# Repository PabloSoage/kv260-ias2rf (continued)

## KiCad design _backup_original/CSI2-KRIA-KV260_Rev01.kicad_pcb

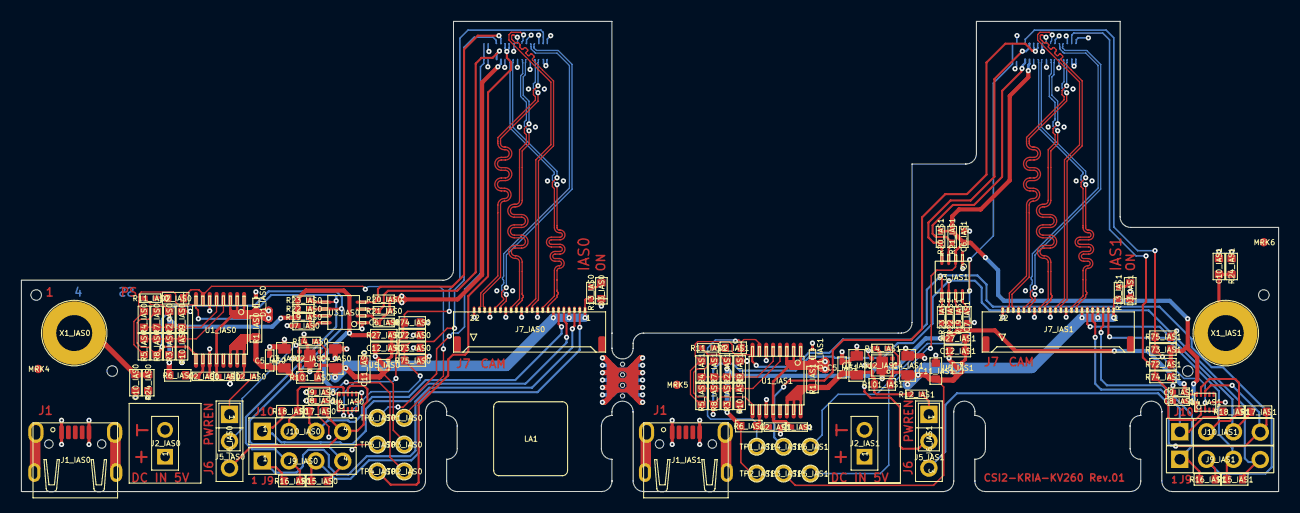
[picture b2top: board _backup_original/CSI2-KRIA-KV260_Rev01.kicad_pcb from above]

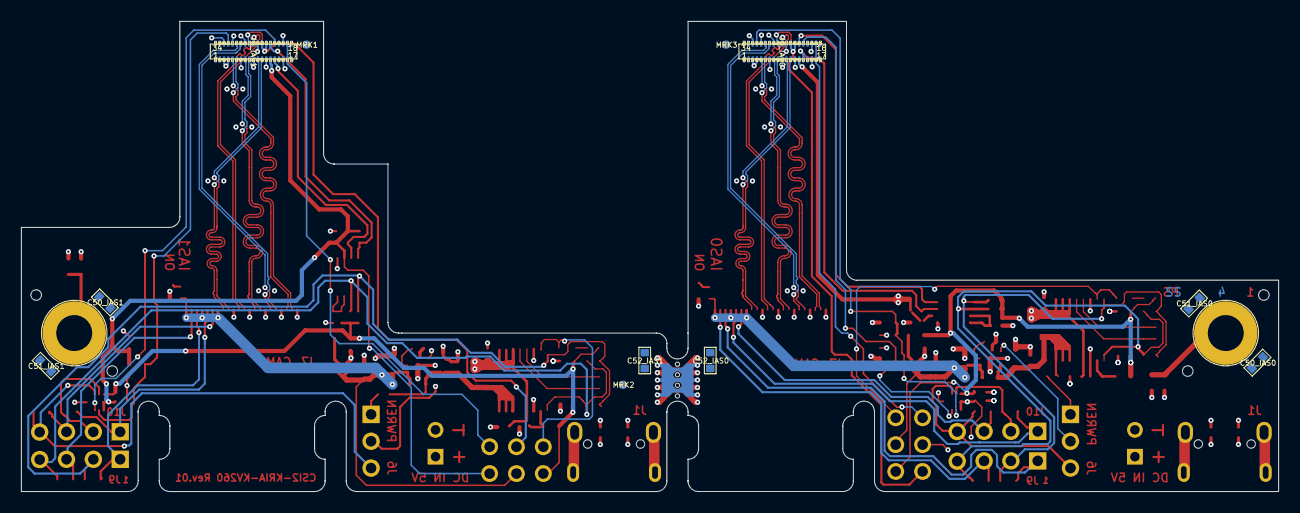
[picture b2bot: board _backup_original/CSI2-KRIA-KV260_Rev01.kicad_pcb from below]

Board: 4 copper layers, 119.0 x 44.5 mm, 145 parts (12 on the bottom side), 82 nets.

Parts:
C1_IAS0, C1_IAS1, C2_IAS0, C2_IAS1: NL; C-0402_0.55
C3_IAS0, C3_IAS1, C4_IAS0, C4_IAS1: 10u; C-0805_1.4
C5_IAS0, C5_IAS1, C6_IAS0, C6_IAS1, C8_IAS0, C8_IAS1, C9_IAS0, C9_IAS1: 100n; C-0402_0.55
C7_IAS0, C7_IAS1: 100p; C-0402_0.55
C10_IAS0, C10_IAS1: NL; C-0603_1.0
C11_IAS0, C11_IAS1, C12_IAS0, C12_IAS1, C50_IAS0, C50_IAS1, C51_IAS0, C51_IAS1, C52_IAS0, C52_IAS1: 4u7; C-0603_1.0
D1_IAS0, D1_IAS1: ESD9B5.0ST5G; D-SOD923
D2_IAS0, D2_IAS1: RED; D-0603-LED
D3_IAS0, D3_IAS1: GREEN; D-0603-LED
J1_IAS0, J1_IAS1: USB 2.0 Typ B 90°; J-629105150521
J2_IAS0, J2_IAS1: CON1x2; CON 1x2 RM2.54
J5_IAS0, J5_IAS1: Jumper; J-JUMPER-2.54
J6_IAS0, J6_IAS1: CON1x3; CON 1x3 RM2.54
J7_IAS0, J7_IAS1: CON FFC22_Inverted; J-FH55-22S-0.5SH - Inverted Pins
J8_IAS0, J8_IAS1: BM20B(0.8)-34DP-0.4V(51); J-BM20B(0.8)-34DP
J9_IAS0, J9_IAS1, J10_IAS0, J10_IAS1: CON1x4; CON 1x4 RM2.54
LA1: LABEL 7x7mm; PCB LABEL 7x7
MRK1, MRK2, MRK3: Marker Single Layer; PCB_Marker_Pad_top
MRK4, MRK5, MRK6: Marker Single Layer; PCB_MARKER_PAD_TOP
R1_IAS0, R1_IAS1, R3_IAS0, R3_IAS1, R9_IAS0, R9_IAS1, R15_IAS0, R15_IAS1, R16_IAS0, R16_IAS1, R24_IAS0, R24_IAS1, R27_IAS0, R27_IAS1: 0R0; R-0603_0.6
R2_IAS0, R2_IAS1, R4_IAS0, R4_IAS1, R5_IAS0, R5_IAS1, R6_IAS0, R6_IAS1, R7_IAS0, R7_IAS1, R8_IAS0, R8_IAS1, R10_IAS0, R10_IAS1, R17_IAS0, R17_IAS1, R18_IAS0, R18_IAS1, R72_IAS0, R72_IAS1, R73_IAS0, R73_IAS1, R74_IAS0, R74_IAS1, R75_IAS0, R75_IAS1, R101_IAS0, R101_IAS1: NL; R-0603_0.6
R11_IAS0, R11_IAS1: NL; R-0402_0.4
R12_IAS0: 270k; R-0402_0.4
R12_IAS1: 270K; R-0402_0.4
R13_IAS0, R13_IAS1: 3k3; R-0402_0.4
R14_IAS0, R14_IAS1: 51k; R-0402_0.4
R19_IAS0, R19_IAS1: 200k; R-0402_0.4
R20_IAS0, R20_IAS1, R21_IAS0, R21_IAS1, R22_IAS0, R22_IAS1, R23_IAS0, R23_IAS1: 2k0; R-0402_0.4
T1: PCB Text TOP; PCB TEXTFIELD TOP 2
T2: PCB Text BOT; PCB TEXTFIELD BOT 2
TP1_IAS0, TP1_IAS1, TP2_IAS0, TP2_IAS1, TP3_IAS0, TP3_IAS1, TP4_IAS0, TP4_IAS1, TP5_IAS0, TP5_IAS1, TP6_IAS0, TP6_IAS1: TP; TP_16_10
U1_IAS0, U1_IAS1: INA260AIPWR; IC-TSSOP16 6.4x5.1x1.2
U2_IAS0, U2_IAS1: TPS25200DRVT; IC-DFN06_2.0x2.0x0.8
U3_IAS0, U3_IAS1: PCA9306DCTR; IC-TSSOP8_3.15x4.25x1.3
U4_IAS0, U4_IAS1: NTB0104GU12,115; IC-XQFN12_1.7x2x0.5
U5_IAS0, U5_IAS1: NCP114AMX330TCG; IC-XDFN4_1.0x1.0x0.6
X1_IAS0, X1_IAS1: Hole; HOLE-3.4-6.0-DK

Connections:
B7-CSI2-TXC_IAS0_N: J7_IAS0.14, J8_IAS0.8
B7-CSI2-TXC_IAS0_P: J7_IAS0.15, J8_IAS0.7
B7-CSI2-TXC_IAS1_N: J7_IAS1.14, J8_IAS1.8
B7-CSI2-TXC_IAS1_P: J7_IAS1.15, J8_IAS1.7
B7-CSI2-TXD0_IAS0_N: J7_IAS0.20, J8_IAS0.5
B7-CSI2-TXD0_IAS0_P: J7_IAS0.21, J8_IAS0.4
B7-CSI2-TXD0_IAS1_N: J7_IAS1.20, J8_IAS1.5
B7-CSI2-TXD0_IAS1_P: J7_IAS1.21, J8_IAS1.4
B7-CSI2-TXD1_IAS0_N: J7_IAS0.17, J8_IAS0.29
B7-CSI2-TXD1_IAS0_P: J7_IAS0.18, J8_IAS0.30
B7-CSI2-TXD1_IAS1_N: J7_IAS1.17, J8_IAS1.29
B7-CSI2-TXD1_IAS1_P: J7_IAS1.18, J8_IAS1.30
B7-CSI2-TXD2_IAS0_N: J7_IAS0.11, J8_IAS0.26
B7-CSI2-TXD2_IAS0_P: J7_IAS0.12, J8_IAS0.27
B7-CSI2-TXD2_IAS1_N: J7_IAS1.11, J8_IAS1.26
B7-CSI2-TXD2_IAS1_P: J7_IAS1.12, J8_IAS1.27
B7-CSI2-TXD3_IAS0_N: J7_IAS0.8, J8_IAS0.11
B7-CSI2-TXD3_IAS0_P: J7_IAS0.9, J8_IAS0.10
B7-CSI2-TXD3_IAS1_N: J7_IAS1.8, J8_IAS1.11
B7-CSI2-TXD3_IAS1_P: J7_IAS1.9, J8_IAS1.10
C-GND_IAS0: C10_IAS0.2, J1_IAS0.6, J1_IAS0.7, J1_IAS0.8, J1_IAS0.9, R24_IAS0.1, X1_IAS0.1
C-GND_IAS1: C10_IAS1.2, J1_IAS1.6, J1_IAS1.7, J1_IAS1.8, J1_IAS1.9, R24_IAS1.1, X1_IAS1.1
EXT-GPIO0-I2C-SCL_IAS0: J7_IAS0.2, J9_IAS0.3, R15_IAS0.1
EXT-GPIO0-I2C-SCL_IAS1: J7_IAS1.2, J9_IAS1.3, R15_IAS1.1
EXT-GPIO1-I2C-SDA_IAS0: J7_IAS0.3, J9_IAS0.1, R16_IAS0.1
EXT-GPIO1-I2C-SDA_IAS1: J7_IAS1.3, J9_IAS1.1, R16_IAS1.1
EXT-GPIO2_IAS0: J7_IAS0.5, J10_IAS0.1, R18_IAS0.1
EXT-GPIO2_IAS1: J7_IAS1.5, J10_IAS1.1, R18_IAS1.1
EXT-GPIO3_IAS0: J7_IAS0.6, J10_IAS0.3, R17_IAS0.1
EXT-GPIO3_IAS1: J7_IAS1.6, J10_IAS1.3, R17_IAS1.1
GND: C1_IAS0.2, C1_IAS1.2, C2_IAS0.2, C2_IAS1.2, C3_IAS0.2, C3_IAS1.2, C4_IAS0.2, C4_IAS1.2, C5_IAS0.2, C5_IAS1.2, C6_IAS0.2, C6_IAS1.2, C7_IAS0.2, C7_IAS1.2, C8_IAS0.2, C8_IAS1.2, C9_IAS0.2, C9_IAS1.2, C10_IAS0.1, C10_IAS1.1, C11_IAS0.2, C11_IAS1.2, C12_IAS0.2, C12_IAS1.2, D1_IAS0.A, D1_IAS1.A, D3_IAS0.K, D3_IAS1.K, J1_IAS0.5, J1_IAS1.5, J2_IAS0.2, J2_IAS1.2, J7_IAS0.10, J7_IAS0.13, J7_IAS0.16, J7_IAS0.19, J7_IAS0.22, J7_IAS1.10, J7_IAS1.13, J7_IAS1.16, J7_IAS1.19, J7_IAS1.22, J8_IAS0.2, J8_IAS0.3, J8_IAS0.6, J8_IAS0.9, J8_IAS0.12, J8_IAS0.16, J8_IAS0.19, J8_IAS0.25, J8_IAS0.28, J8_IAS0.31, J8_IAS0.33, J8_IAS1.2, J8_IAS1.3, J8_IAS1.6, J8_IAS1.9, J8_IAS1.12, J8_IAS1.16, J8_IAS1.19, J8_IAS1.25, J8_IAS1.28, J8_IAS1.31, J8_IAS1.33, R9_IAS0.1, R9_IAS1.1, R10_IAS0.1, R10_IAS1.1, R14_IAS0.1, R14_IAS1.1, R24_IAS0.2, R24_IAS1.2, R74_IAS0.1, R74_IAS1.1, R75_IAS0.1, R75_IAS1.1, U1_IAS0.6, U1_IAS0.11, U1_IAS1.6, U1_IAS1.11, U2_IAS0.5, U2_IAS0.7, U2_IAS1.5, U2_IAS1.7, U3_IAS0.1, U3_IAS1.1, U4_IAS0.6, U4_IAS1.6, U5_IAS0.2, U5_IAS0.5, U5_IAS1.2, U5_IAS1.5
GPIO2_3V3_IAS0: J10_IAS0.2, R18_IAS0.2, U4_IAS0.10
GPIO2_3V3_IAS1: J10_IAS1.2, R18_IAS1.2, U4_IAS1.10
GPIO2_IAS0: J8_IAS0.32, R72_IAS0.1, R74_IAS0.2, U4_IAS0.2
GPIO2_IAS1: J8_IAS1.32, R72_IAS1.1, R74_IAS1.2, U4_IAS1.2
GPIO3_3V3_IAS0: J6_IAS0.3, J10_IAS0.4, R17_IAS0.2, U4_IAS0.9
GPIO3_3V3_IAS1: J6_IAS1.3, J10_IAS1.4, R17_IAS1.2, U4_IAS1.9
I2C_SCL_3V3_IAS0: J9_IAS0.4, R7_IAS0.1, R8_IAS0.1, R15_IAS0.2, R22_IAS0.1, U1_IAS0.9, U3_IAS0.6
I2C_SCL_3V3_IAS1: J9_IAS1.4, R7_IAS1.1, R8_IAS1.1, R15_IAS1.2, R22_IAS1.1, U1_IAS1.9, U3_IAS1.6
I2C_SCL_IAS0: J8_IAS0.14, R21_IAS0.2, U3_IAS0.3
I2C_SCL_IAS1: J8_IAS1.14, R21_IAS1.2, U3_IAS1.3
I2C_SDA_3V3_IAS0: J9_IAS0.2, R4_IAS0.1, R5_IAS0.1, R16_IAS0.2, R23_IAS0.1, U1_IAS0.8, U3_IAS0.5
I2C_SDA_3V3_IAS1: J9_IAS1.2, R4_IAS1.1, R5_IAS1.1, R16_IAS1.2, R23_IAS1.1, U1_IAS1.8, U3_IAS1.5
I2C_SDA_IAS0: J8_IAS0.22, R20_IAS0.2, U3_IAS0.4
I2C_SDA_IAS1: J8_IAS1.22, R20_IAS1.2, U3_IAS1.4
INA260-A0_IAS0: R2_IAS0.2, R4_IAS0.2, R7_IAS0.2, R9_IAS0.2, U1_IAS0.5
INA260-A0_IAS1: R2_IAS1.2, R4_IAS1.2, R7_IAS1.2, R9_IAS1.2, U1_IAS1.5
INA260-A1_IAS0: R3_IAS0.2, R5_IAS0.2, R8_IAS0.2, R10_IAS0.2, U1_IAS0.4
INA260-A1_IAS1: R3_IAS1.2, R5_IAS1.2, R8_IAS1.2, R10_IAS1.2, U1_IAS1.4
NetC2_IAS0_1: C2_IAS0.1, R6_IAS0.2, U1_IAS0.10
NetC2_IAS1_1: C2_IAS1.1, R6_IAS1.2, U1_IAS1.10
NetC7_IAS0_1: C7_IAS0.1, R19_IAS0.1, U3_IAS0.7, U3_IAS0.8
NetC7_IAS1_1: C7_IAS1.1, R19_IAS1.1, U3_IAS1.7, U3_IAS1.8
NetC12_IAS0_1: C12_IAS0.1, R27_IAS0.1, U5_IAS0.1
NetC12_IAS1_1: C12_IAS1.1, R27_IAS1.1, U5_IAS1.1
NetD2_IAS0_A: D2_IAS0.A, R11_IAS0.2
NetD2_IAS0_K: D2_IAS0.K, TP1_IAS0.1, U1_IAS0.7
NetD2_IAS1_A: D2_IAS1.A, R11_IAS1.2
NetD2_IAS1_K: D2_IAS1.K, TP1_IAS1.1, U1_IAS1.7
NetD3_IAS0_A: D3_IAS0.A, R13_IAS0.2
NetD3_IAS1_A: D3_IAS1.A, R13_IAS1.2
NetJ6_IAS0_1: J6_IAS0.1, R12_IAS0.2
NetJ6_IAS0_2: J6_IAS0.2, U2_IAS0.4
NetJ6_IAS1_1: J6_IAS1.1, R12_IAS1.2
NetJ6_IAS1_2: J6_IAS1.2, U2_IAS1.4
NetR14_IAS0_2: R14_IAS0.2, U2_IAS0.2
NetR14_IAS1_2: R14_IAS1.2, U2_IAS1.2
PWDN_IAS0: J8_IAS0.21, R73_IAS0.1, R75_IAS0.2, U4_IAS0.3
PWDN_IAS1: J8_IAS1.21, R73_IAS1.1, R75_IAS1.2, U4_IAS1.3
VCC1V2_IAS0: J8_IAS0.23, J8_IAS0.24, TP4_IAS0.1
VCC1V2_IAS1: J8_IAS1.23, J8_IAS1.24, TP4_IAS1.1
VCC1V8_IAS0: C6_IAS0.1, C8_IAS0.1, J8_IAS0.13, R20_IAS0.1, R21_IAS0.1, R72_IAS0.2, R73_IAS0.2, TP5_IAS0.1, U3_IAS0.2, U4_IAS0.1, U4_IAS0.12
VCC1V8_IAS1: C6_IAS1.1, C8_IAS1.1, J8_IAS1.13, R20_IAS1.1, R21_IAS1.1, R72_IAS1.2, R73_IAS1.2, TP5_IAS1.1, U3_IAS1.2, U4_IAS1.1, U4_IAS1.12
VCC2V75_IAS0: J8_IAS0.17, J8_IAS0.18, TP6_IAS0.1
VCC2V75_IAS1: J8_IAS1.17, J8_IAS1.18, TP6_IAS1.1
VCC3V3_IAS0: C9_IAS0.1, R2_IAS0.1, R3_IAS0.1, R6_IAS0.1, R11_IAS0.1, R19_IAS0.2, R22_IAS0.2, R23_IAS0.2, R27_IAS0.2, TP2_IAS0.1, U4_IAS0.11
VCC3V3_IAS1: C9_IAS1.1, R2_IAS1.1, R3_IAS1.1, R6_IAS1.1, R11_IAS1.1, R19_IAS1.2, R22_IAS1.2, R23_IAS1.2, R27_IAS1.2, TP2_IAS1.1, U4_IAS1.11
VCC5V-CAM_IAS0: C3_IAS0.1, C5_IAS0.1, R1_IAS0.1, R12_IAS0.1, R101_IAS0.2, U1_IAS0.14, U1_IAS0.15, U1_IAS0.16, U2_IAS0.6
VCC5V-CAM_IAS1: C3_IAS1.1, C5_IAS1.1, R1_IAS1.1, R12_IAS1.1, R101_IAS1.2, U1_IAS1.14, U1_IAS1.15, U1_IAS1.16, U2_IAS1.6
VCC5V-EXT: C1_IAS0.1, C1_IAS1.1, D1_IAS0.K, D1_IAS1.K, J1_IAS0.1, J1_IAS1.1, J2_IAS0.1, J2_IAS1.1, R1_IAS0.2, R1_IAS1.2, U1_IAS0.1, U1_IAS0.2, U1_IAS0.3, U1_IAS0.12, U1_IAS1.1, U1_IAS1.2, U1_IAS1.3, U1_IAS1.12
VCC-EXT-IN_IAS0: C4_IAS0.1, C11_IAS0.1, J7_IAS0.1, J7_IAS0.4, J7_IAS0.7, R13_IAS0.1, R101_IAS0.1, TP3_IAS0.1, U2_IAS0.1, U5_IAS0.3, U5_IAS0.4
VCC-EXT-IN_IAS1: C4_IAS1.1, C11_IAS1.1, J7_IAS1.1, J7_IAS1.4, J7_IAS1.7, R13_IAS1.1, R101_IAS1.1, TP3_IAS1.1, U2_IAS1.1, U5_IAS1.3, U5_IAS1.4

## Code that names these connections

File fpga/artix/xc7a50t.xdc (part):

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#   Note: LVDS_25 inputs are legal in a 3.3 V bank only with DIFF_TERM = FALSE
#         and external 100 ohm termination (R105, R106, R1101..R1110).
# ------------------------------------------------------------------------------
set_property PACKAGE_PIN N11 [get_ports fpga_clk_p]
set_property PACKAGE_PIN N12 [get_ports fpga_clk_n]
set_property IOSTANDARD  LVDS_25 [get_ports {fpga_clk_p fpga_clk_n}]
set_property DIFF_TERM   FALSE   [get_ports {fpga_clk_p fpga_clk_n}]

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set_property PACKAGE_PIN T8  [get_ports {adcr_d_n[6]}]
set_property PACKAGE_PIN R6  [get_ports {adcr_d_p[7]}]
set_property PACKAGE_PIN R7  [get_ports {adcr_d_n[7]}]
set_property PACKAGE_PIN M6  [get_ports adcr_or_p]
set_property PACKAGE_PIN N6  [get_ports adcr_or_n]
set_property PACKAGE_PIN N14 [get_ports adcr_dco_n]
set_property PACKAGE_PIN P14 [get_ports adcr_dco_p]

set_property IOSTANDARD LVDS_25 [get_ports {adcr_d_p[*] adcr_d_n[*] adcr_or_p adcr_or_n adcr_dco_n adcr_dco_p}]
set_property DIFF_TERM  FALSE   [get_ports {adcr_d_p[*] adcr_d_n[*] adcr_or_p adcr_or_n adcr_dco_n adcr_dco_p}]

# AD9253 14-bit SDR ADC LVDS Inputs (Bank 14, VCCO = 3.3 V, ext 100 ohm -> DIFF_TERM = FALSE)
set_property PACKAGE_PIN P10 [get_ports adcs_dco_p]
set_property PACKAGE_PIN P11 [get_ports adcs_dco_n]
set_property PACKAGE_PIN N9  [get_ports adcs_fco_p]
set_property PACKAGE_PIN P9  [get_ports adcs_fco_n]
set_property PACKAGE_PIN P8  [get_ports adcs_d0_p]
set_property PACKAGE_PIN R8  [get_ports adcs_d0_n]
set_property PACKAGE_PIN R5  [get_ports adcs_d1_p]
set_property PACKAGE_PIN T5  [get_ports adcs_d1_n]
set_property IOSTANDARD  LVDS_25 [get_ports {adcs_dco_p adcs_dco_n adcs_fco_p adcs_fco_n adcs_d0_p adcs_d0_n adcs_d1_p adcs_d1_n}]
set_property DIFF_TERM   FALSE   [get_ports {adcs_dco_p adcs_dco_n adcs_fco_p adcs_fco_n adcs_d0_p adcs_d0_n adcs_d1_p adcs_d1_n}]

# IAS1 Downlink RX (Kria -> Artix): LINK_TX_CLK (SRCC) & LINK_TX_D0
set_property PACKAGE_PIN N13 [get_ports link_tx_clk_p]
set_property PACKAGE_PIN P13 [get_ports link_tx_clk_n]
set_property PACKAGE_PIN M16 [get_ports link_tx_d0_p]
set_property PACKAGE_PIN N16 [get_ports link_tx_d0_n]
set_property IOSTANDARD  LVDS_25 [get_ports {link_tx_clk_p link_tx_clk_n link_tx_d0_p link_tx_d0_n}]
set_property DIFF_TERM   FALSE   [get_ports {link_tx_clk_p link_tx_clk_n link_tx_d0_p link_tx_d0_n}]

# ------------------------------------------------------------------------------
# Bank 34 (VCCO = 2.5 V): IAS1 Uplink TX (Artix -> Kria)
# ------------------------------------------------------------------------------
set_property PACKAGE_PIN N3  [get_ports link_rx_clk_p]
set_property PACKAGE_PIN N2  [get_ports link_rx_clk_n]
set_property PACKAGE_PIN L4  [get_ports link_rx_d0_p]
set_property PACKAGE_PIN M4  [get_ports link_rx_d0_n]
set_property PACKAGE_PIN M2  [get_ports link_rx_d1_p]
set_property PACKAGE_PIN M1  [get_ports link_rx_d1_n]
set_property IOSTANDARD  LVDS_25 [get_ports {link_rx_clk_p link_rx_clk_n link_rx_d0_p link_rx_d0_n link_rx_d1_p link_rx_d1_n}]

# Rev06 Dedicated Ethernet SGMII PHY (Final Routed Pins)
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set_property IOSTANDARD  LVDS_25 [get_ports {eth_sgrx_p eth_sgrx_n}]
set_property DIFF_TERM   TRUE    [get_ports {eth_sgrx_p eth_sgrx_n}]

set_property PACKAGE_PIN P1  [get_ports eth_mdc]
set_property IOSTANDARD  LVCMOS25 [get_ports eth_mdc]
set_property SLEW        SLOW     [get_ports eth_mdc]
set_property DRIVE       4        [get_ports eth_mdc]

#   Bank 14 (VCCO = 3.3 V): MDIO open-drain (R1213 1.5k -> 2.5V DVDDRG, do not use EMCCLK), RST_N pulled up via R1214
set_property PACKAGE_PIN M15 [get_ports eth_mdio]
set_property PACKAGE_PIN K13 [get_ports eth_rst_n]
set_property IOSTANDARD  LVCMOS33 [get_ports {eth_mdio eth_rst_n}]
set_property SLEW        SLOW     [get_ports eth_mdio]
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# Bank 15 (VCCO = 3.3 V): Adapter Pmod J1102
# ------------------------------------------------------------------------------
set_property PACKAGE_PIN H16 [get_ports pmod_cs_n]
set_property PACKAGE_PIN G16 [get_ports pmod_mosi]
set_property PACKAGE_PIN J15 [get_ports pmod_miso]
set_property PACKAGE_PIN D13 [get_ports pmod_sclk]
set_property PACKAGE_PIN J16 [get_ports beam_strobe]
set_property PACKAGE_PIN H14 [get_ports pps_sync]
set_property PACKAGE_PIN G15 [get_ports pmod_spare1]
set_property PACKAGE_PIN G11 [get_ports pmod_spare2]
set_property IOSTANDARD  LVCMOS33 [get_ports {pmod_cs_n pmod_mosi pmod_miso pmod_sclk beam_strobe pps_sync pmod_spare1 pmod_spare2}]

# AD9708 8-bit Radar DAC (Bank 15, VCCO = 3.3 V)
set_property PACKAGE_PIN C13 [get_ports dacr_clk]
set_property PACKAGE_PIN A14 [get_ports {dacr_d[0]}]
set_property PACKAGE_PIN A13 [get_ports {dacr_d[1]}]
set_property PACKAGE_PIN A12 [get_ports {dacr_d[2]}]
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set_property PACKAGE_PIN C16 [get_ports {dacs_d[11]}]
set_property PACKAGE_PIN A15 [get_ports {dacs_d[12]}]
set_property PACKAGE_PIN B16 [get_ports {dacs_d[13]}]
set_property PACKAGE_PIN E11 [get_ports dacs_iqclk]
set_property PACKAGE_PIN D10 [get_ports dacs_iqreset]
set_property PACKAGE_PIN G12 [get_ports dacs_iqsel]
set_property PACKAGE_PIN F12 [get_ports dacs_iqwrt]
set_property IOSTANDARD  LVCMOS33 [get_ports {dacs_d[*] dacs_iqclk dacs_iqreset dacs_iqsel dacs_iqwrt}]

# RF Switches & Si549 Clock Mux/I2C (Bank 15, VCCO = 3.3 V)
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set_property PACKAGE_PIN C9  [get_ports {sw_ctrl[1]}]
set_property PACKAGE_PIN B9  [get_ports {sw_ctrl[2]}]
set_property PACKAGE_PIN B12 [get_ports {sw_ctrl[3]}]
set_property PACKAGE_PIN D9  [get_ports xo_scl]
set_property PACKAGE_PIN C14 [get_ports xo_sda]
set_property PACKAGE_PIN D8  [get_ports clk_sel]
set_property IOSTANDARD  LVCMOS33 [get_ports {sw_ctrl[*] xo_scl xo_sda clk_sel}]

# ------------------------------------------------------------------------------
# Bank 35 (VCCO = 1.8 V): Housekeeping I2C, Alert, Carrier IRQ, Conv SPI, 8x ADAR1000
# ------------------------------------------------------------------------------
set_property PACKAGE_PIN K5  [get_ports hk_scl]
set_property PACKAGE_PIN J5  [get_ports hk_sda]
set_property PACKAGE_PIN K2  [get_ports hk_alert_n]
set_property PACKAGE_PIN H5  [get_ports fpga_irq]
set_property IOSTANDARD  LVCMOS18 [get_ports {hk_scl hk_sda hk_alert_n fpga_irq}]

# Shared Converter 3-wire SPI (AD9484 CSB_R, AD9253 CSB_S)
set_property PACKAGE_PIN J4  [get_ports conv_spi_csb_r]
set_property PACKAGE_PIN L2  [get_ports conv_spi_csb_s]
set_property PACKAGE_PIN K3  [get_ports conv_spi_sclk]
set_property PACKAGE_PIN L3  [get_ports conv_spi_sdio]
set_property IOSTANDARD  LVCMOS18 [get_ports {conv_spi_csb_r conv_spi_csb_s conv_spi_sclk conv_spi_sdio}]

# 8x ADAR1000 Beamformer Ribbon J1103 (Bank 35 LVCMOS18, SLEW SLOW + DRIVE 4 for ribbon SI)
set_property PACKAGE_PIN J1  [get_ports adar_sclk]
set_property PACKAGE_PIN J3  [get_ports adar_sdio]
set_property PACKAGE_PIN K1  [get_ports adar_sdo]
set_property PACKAGE_PIN A5  [get_ports {adar_csb[0]}]
set_property PACKAGE_PIN C6  [get_ports {adar_csb[1]}]
set_property PACKAGE_PIN C4  [get_ports {adar_csb[2]}]
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
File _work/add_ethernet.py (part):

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    "C1202": ("Device:C", "27p", C0402, "ETH_XO", "GND", "crystal load"),
    "L1201": ("Device:L", "2.2u", "Inductor_SMD:L_0805_2012Metric", "ETH_REGOUT", "ETH_1V0", "switching regulator inductor"),
    "C1203": ("Device:C", "10u", C0805, "ETH_1V0", "GND", "1.0 V output"),
    "C1204": ("Device:C", "100n", C0402, "ETH_1V0", "GND", "AVDD10 pin 4"),
    "C1205": ("Device:C", "100n", C0402, "ETH_1V0", "GND", "AVDD10 pin 9"),
    "C1206": ("Device:C", "100n", C0402, "ETH_1V0", "GND", "AVDD10 pin 47"),
    "C1207": ("Device:C", "100n", C0402, "ETH_1V0", "GND", "DVDD10 pin 22"),
    "FB1201": ("Device:FerriteBead", "600R@100MHz", "Inductor_SMD:L_0603_1608Metric", "+3V3_D", "ETH_AVDD33", "AVDD33 filter"),
    "C1208": ("Device:C", "10u", C0805, "ETH_AVDD33", "GND", "AVDD33 bulk"),
    "C1209": ("Device:C", "100n", C0402, "ETH_AVDD33", "GND", "AVDD33 pin 1"),
    "C1210": ("Device:C", "100n", C0402, "ETH_AVDD33", "GND", "AVDD33 pin 12"),
    "C1211": ("Device:C", "100n", C0402, "+3V3_D", "GND", "DVDD33 pin 30"),
    "C1212": ("Device:C", "10u", C0805, "+3V3_D", "GND", "VDD_REG pin 31, the regulator's input"),
    "C1213": ("Device:C", "100n", C0402, "+3V3_D", "GND", "VDD_REG pin 31"),
    "C1214": ("Device:C", "1u", C0402, "ETH_DVDDRG", "GND", "DVDD_RG, the internal 2.5 V LDO's output"),
    "C1215": ("Device:C", "100n", C0402, "ETH_DVDDRG", "GND", "DVDD_RG pin 29"),
    "R1202": ("Device:R", "4.7k", R0402, "ETH_LED0", "+3V3_D", "strap PHYAD0 = 1"),
    "R1203": ("Device:R", "4.7k", R0402, "ETH_LED1", "+3V3_D", "strap CFG_LDO0 = 1"),
    "R1204": ("Device:R", "4.7k", R0402, "ETH_LED2", "GND", "strap CFG_LDO1 = 0: CFG_LDO = 01, 2.5 V I/O"),
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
